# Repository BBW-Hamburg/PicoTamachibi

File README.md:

# PicoTamachibi
A Tamagotchi like toy based on PRI Pico

- The code is based on a Project from [kevinmcaleer](https://www.youtube.com/@kevinmcaleer28), the [original code can be found on his Github page](https://github.com/kevinmcaleer/picotamachibi)
- Used only for educational purposes
- *Folders:*
- contains needed libraries
- pcb_tamachibi_1-2 contains the KiCad- & gerber-files needed to create the PCBs for this project (not needed inside the Picos storage to run the project)
- raw_assets contains the graphic assets for this project (not needed inside the Picos storage to run the project)

## Setup with VSCode

It is recommended to create a new vscode profile for this type of project to have a clean editor.

VSCode will recommend extensions for this project, all of them are required to run the project.

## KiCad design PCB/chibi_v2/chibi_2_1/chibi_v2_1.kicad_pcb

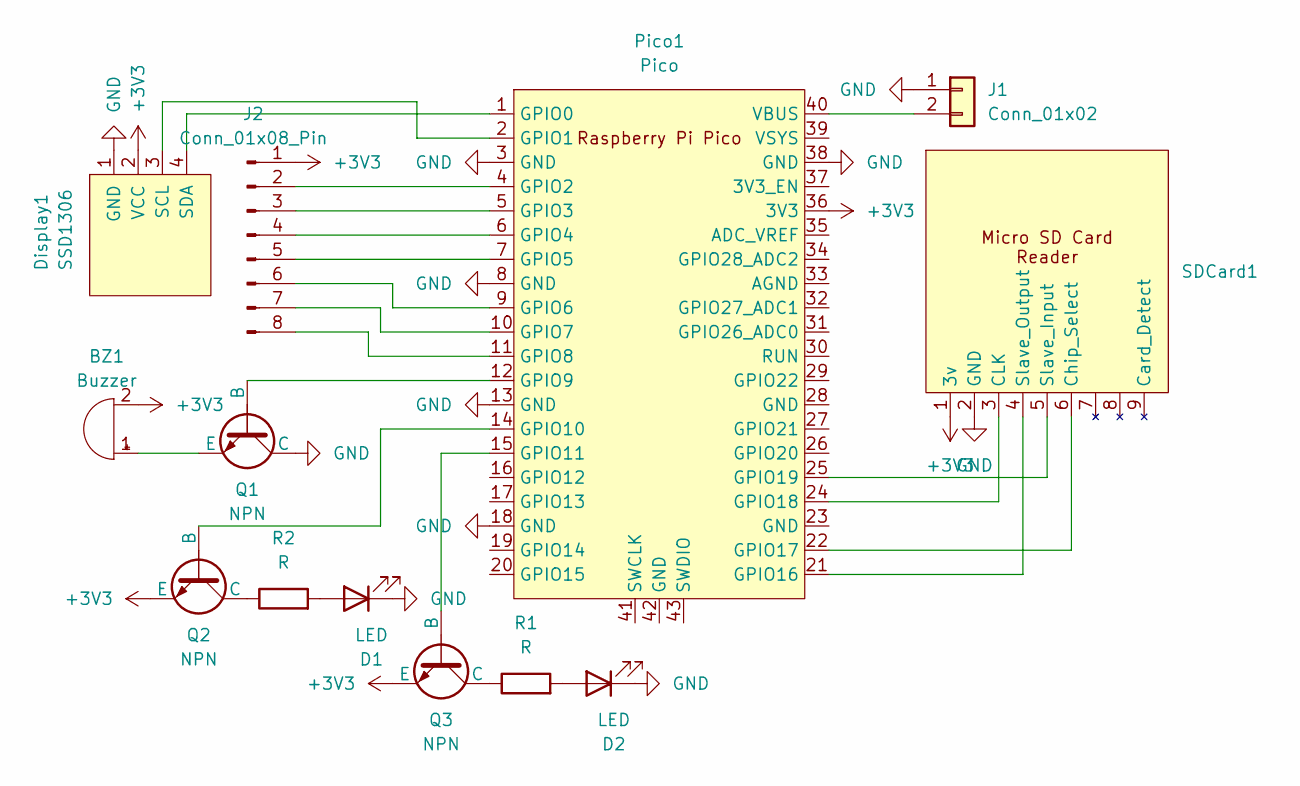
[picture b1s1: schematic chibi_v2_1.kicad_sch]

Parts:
BZ1: Buzzer; Buzzer_12x9.5RM7.6
D1, D2: LED; LED_D1.8mm_W1.8mm_H2.4mm_Horizontal_O1.27mm_Z1.6mm
Display1: SSD1306; 128x64OLED
J1: Conn_01x02; PinHeader_1x02_P2.54mm_Vertical
J2: Conn_01x08_Pin; PinHeader_1x08_P2.54mm_Vertical
Pico1: Pico; RPi_Pico_SMD_TH
Q1, Q2, Q3: NPN; TO92
R1, R2: R; R_Axial_DIN0207_L6.3mm_D2.5mm_P10.16mm_Horizontal
SDCard1: Adafruit_Micro_SD_SPI_or_SDIO_Card_Breakout_Board

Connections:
+3V3: BZ1.2 (-), Display1.2 (VCC), J2.1, Pico1.36 (3V3), Q2.3 (E), Q3.3 (E), SDCard1.1 (3v)
GND: D1.1 (K), D2.1 (K), Display1.1 (GND), J1.1, Pico1.3 (GND), Pico1.8 (GND), Pico1.13 (GND), Pico1.18 (GND), Pico1.38 (GND), Q1.1 (C), SDCard1.2 (GND)
unnamed: BZ1.1 (+), Q1.3 (E)
unnamed: D1.2 (A), R2.2
unnamed: D2.2 (A), R1.2
unnamed: Display1.3 (SCL), Pico1.2 (GPIO1)
unnamed: Display1.4 (SDA), Pico1.1 (GPIO0)
unnamed: J1.2, Pico1.40 (VBUS)
unnamed: J2.2, Pico1.4 (GPIO2)
unnamed: J2.3, Pico1.5 (GPIO3)
unnamed: J2.4, Pico1.6 (GPIO4)
unnamed: J2.5, Pico1.7 (GPIO5)
unnamed: J2.6, Pico1.9 (GPIO6)
unnamed: J2.7, Pico1.10 (GPIO7)
unnamed: J2.8, Pico1.11 (GPIO8)
unnamed: Pico1.12 (GPIO9), Q1.2 (B)
unnamed: Pico1.14 (GPIO10), Q2.2 (B)
unnamed: Pico1.15 (GPIO11), Q3.2 (B)
unnamed: Pico1.21 (GPIO16), SDCard1.4 (Slave_Output)
unnamed: Pico1.22 (GPIO17), SDCard1.6 (Chip_Select)
unnamed: Pico1.24 (GPIO18), SDCard1.3 (CLK)
unnamed: Pico1.25 (GPIO19), SDCard1.5 (Slave_Input)
unnamed: Q2.1 (C), R2.1
unnamed: Q3.1 (C), R1.1

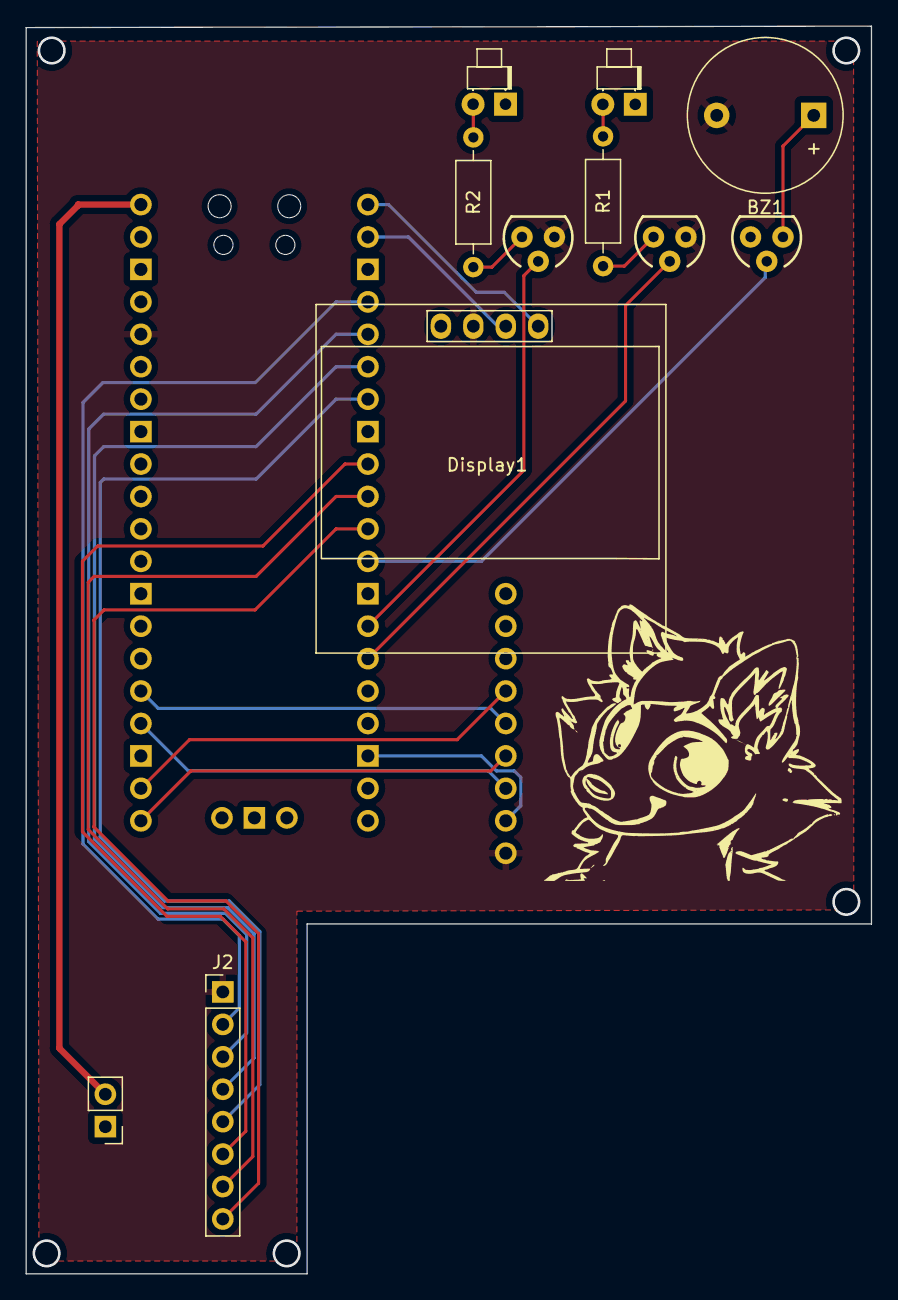
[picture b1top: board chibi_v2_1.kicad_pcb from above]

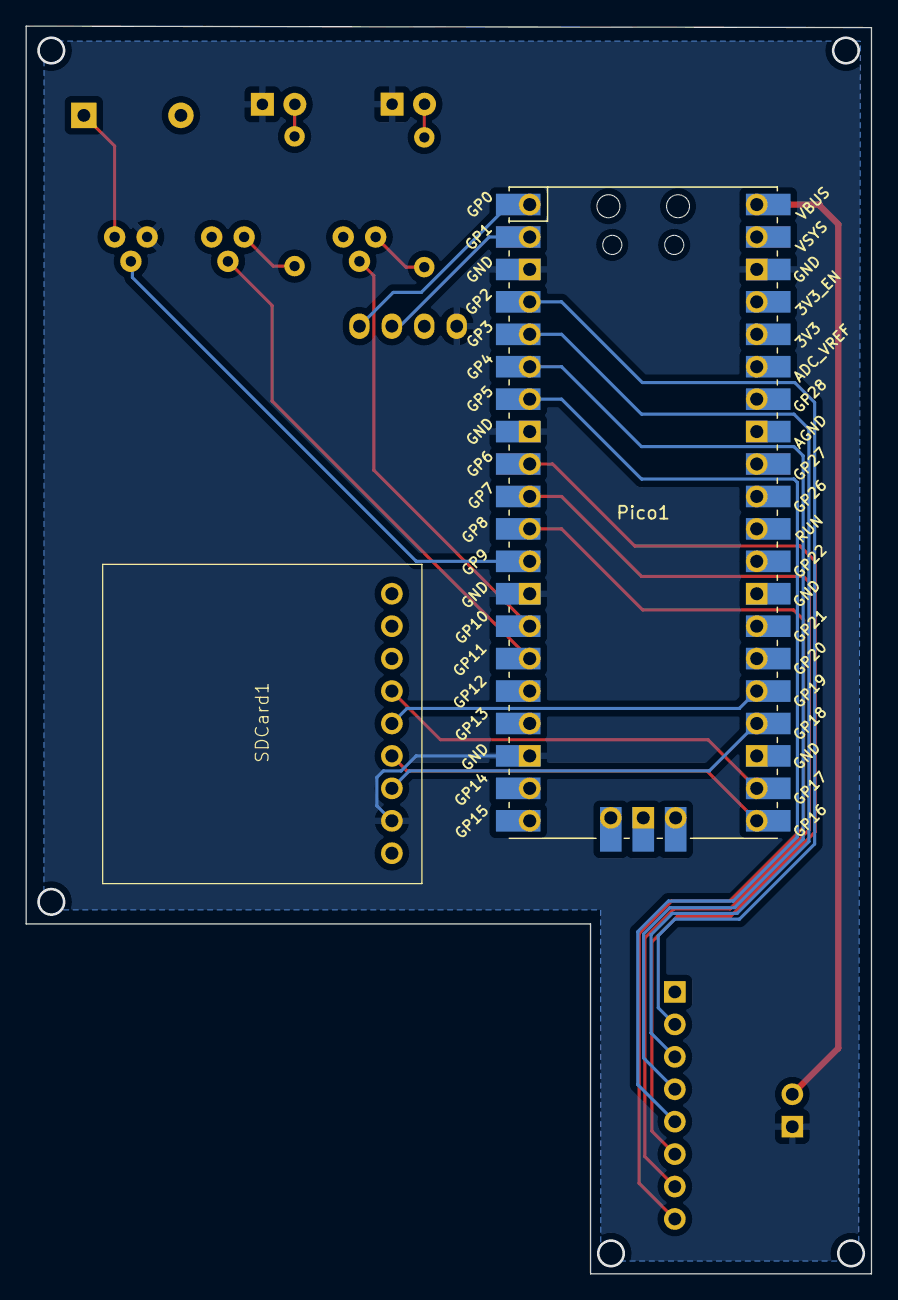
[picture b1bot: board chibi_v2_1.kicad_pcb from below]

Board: 2 copper layers, 66.2 x 97.7 mm, 13 parts (2 on the bottom side), 24 nets.

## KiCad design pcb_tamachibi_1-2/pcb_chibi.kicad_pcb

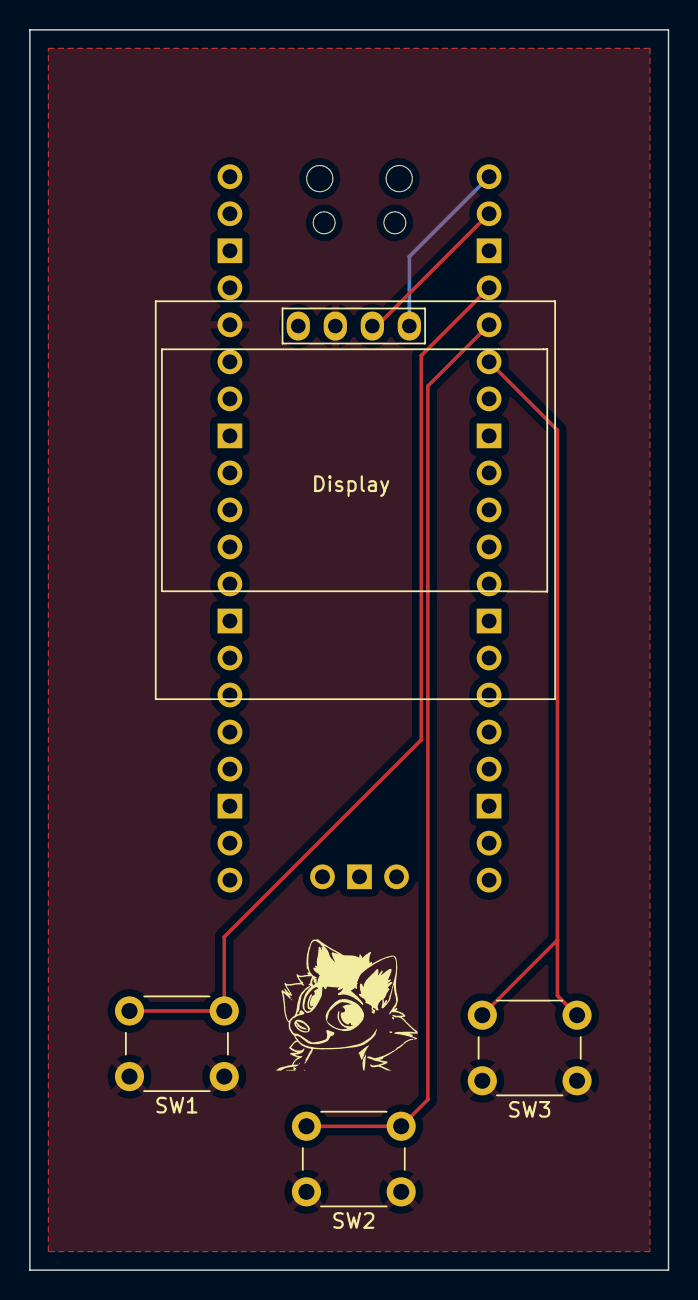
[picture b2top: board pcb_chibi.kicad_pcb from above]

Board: 2 copper layers, 43.8 x 85.1 mm, 5 parts (1 on the bottom side), 7 nets.

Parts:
Display: SSD1306; 128x64OLED
Pico: Pico; RPi_Pico_SMD_TH
SW1, SW2, SW3: SW_Push; SW_PUSH_6mm

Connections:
+3V3: Display.2 (VCC), Pico.36 (3V3), SW1.1, SW2.1, SW3.1
GND: Display.1 (GND), Pico.3 (GND), Pico.8 (GND), Pico.13 (GND), Pico.18 (GND), Pico.23 (GND), Pico.28 (GND), Pico.38 (GND)
unnamed: Display.3 (SCL), Pico.2 (GPIO1)
unnamed: Display.4 (SDA), Pico.1 (GPIO0)
unnamed: Pico.4 (GPIO2), SW1.2
unnamed: Pico.5 (GPIO3), SW2.2
unnamed: Pico.6 (GPIO4), SW3.2

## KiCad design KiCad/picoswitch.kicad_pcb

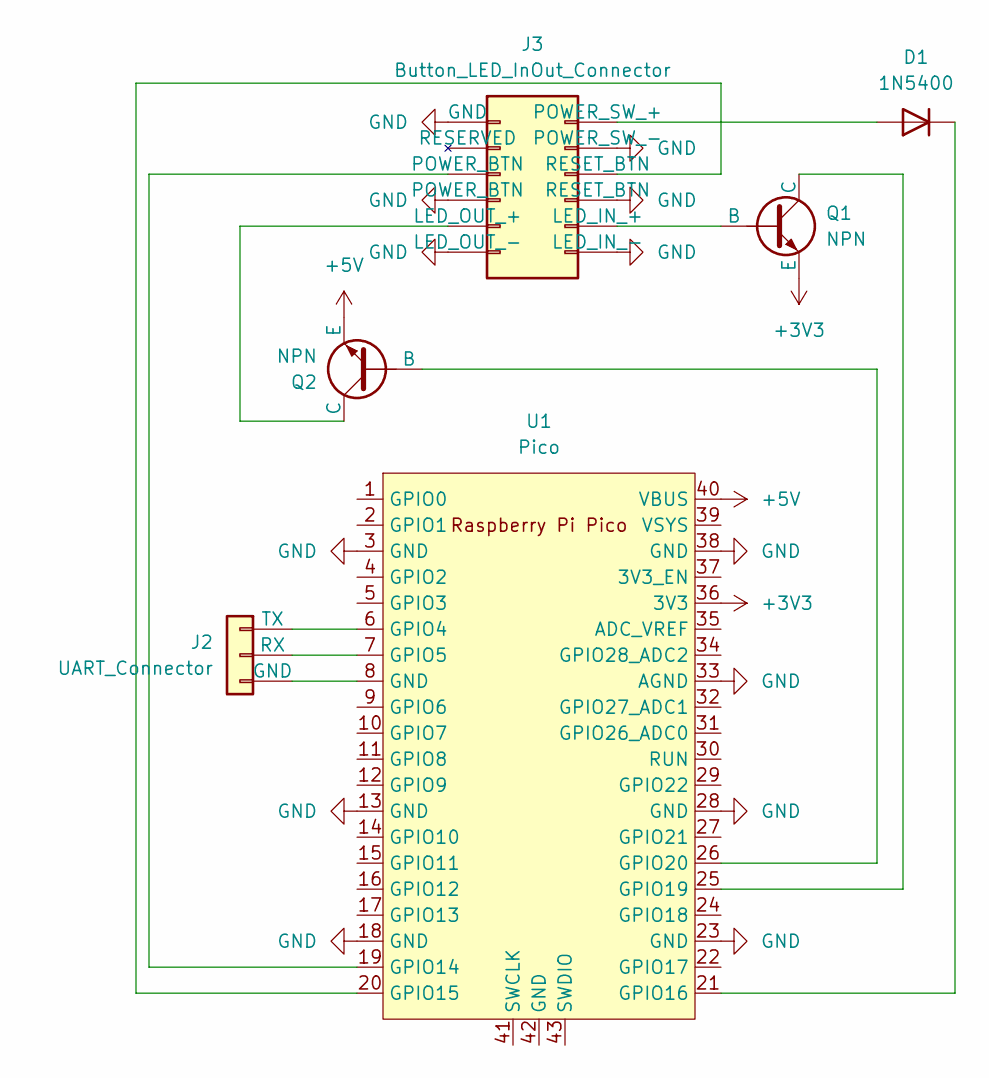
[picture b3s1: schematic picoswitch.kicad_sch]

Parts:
D1: 1N5400; D_DO-201AD_P3.81mm_Vertical_AnodeUp
J2: UART_Connector; PinSocket_1x03_P2.54mm_Vertical
J3: Button_LED_InOut_Connector; PinSocket_2x06_P2.54mm_Vertical
Q1, Q2: NPN; TO-92_Inline
U1: Pico; RPi_Pico_SMD_TH

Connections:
+3V3: Q1.3 (E), U1.36 (3V3)
+5V: Q2.3 (E), U1.40 (VBUS)
GND: J3.1 (GND), J3.4 (POWER_BTN), J3.6 (LED_OUT_-), J3.7 (LED_IN_-), J3.9 (RESET_BTN), J3.11 (POWER_SW_-), U1.3 (GND), U1.13 (GND), U1.18 (GND), U1.23 (GND), U1.28 (GND), U1.33 (AGND), U1.38 (GND)
unnamed: D1.2 (A), J3.12 (POWER_SW_+)
unnamed: D1.1 (K), U1.21 (GPIO16)
unnamed: J2.1 (GND), U1.8 (GND)
unnamed: J2.2 (RX), U1.7 (GPIO5)
unnamed: J2.3 (TX), U1.6 (GPIO4)
unnamed: J3.8 (LED_IN_+), Q1.2 (B)
unnamed: J3.5 (LED_OUT_+), Q2.1 (C)
unnamed: Q1.1 (C), U1.25 (GPIO19)
unnamed: Q2.2 (B), U1.26 (GPIO20)
unnamed: J3.3 (POWER_BTN), U1.19 (GPIO14)
unnamed: J3.10 (RESET_BTN), U1.20 (GPIO15)

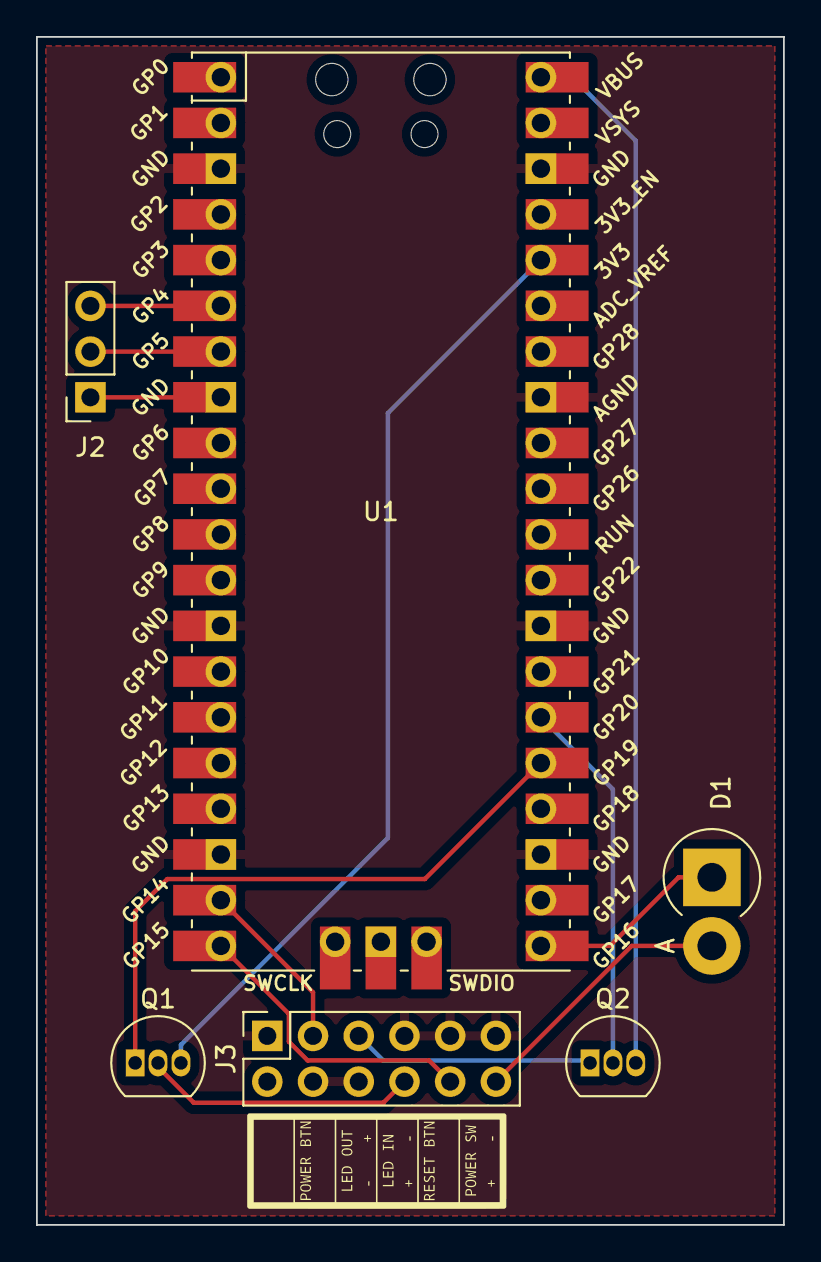
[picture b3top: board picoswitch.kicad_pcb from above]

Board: 2 copper layers, 41.5 x 66.0 mm, 6 parts (0 on the bottom side), 14 nets.

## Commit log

2024-01-19 Fixed UART
2024-01-21 Better PCB
2024-01-21 UART enhancements
2024-01-22 Remove redundant variable
2024-01-26 (Almost) full implementation
2024-01-26 Fixed pico-sdk #1
2024-01-26 Fixed pico-sdk #2
2024-01-26 Emulator and loads and loads of fixes
2024-01-26 More minor fixing
2024-01-26 Change to ETL
2024-01-27 Allocate context on stack
2024-01-27 Increased stack size now that we do everything on stack
2024-01-27 Renamed Animate::get_frame_count() to Animate::get_max_frame_index() for clarity
2024-01-27 Better main loop source mapping
2024-01-27 Increase max length of "health" strings
2024-01-27 Minor ETL tuning
2024-02-01 Fixed windows compilation (hopefully)
2024-02-01 Another attempt at fixing windows builds
2024-02-01 Another attempt
2024-02-01 Added Display::Size::buffer_size()
2024-02-01 Completely revert Windows "fix"
2024-02-01 Use ETL_NO_STL
2024-02-01 Revert last commit
2024-02-01 Enable ETL_USING_CPP20
2024-02-01 Downgrade to C++17
2024-02-01 Do not build emulator by default
2024-02-01 Fixed stack overflow in Event::popup
2024-02-01 Reuse framebuffer in popup() instead of allocating a new one
2024-02-01 Moved Event::tick() inline
2024-02-09 Initial branch commit
2024-02-11 Lots of fixes including bounce animation
2024-02-11 Fixed animation repeat check
2024-02-14 initial commit
    Added files form localy working version
2024-02-14 Update README.md
    updated text
2024-02-15 one new line for demonstarion purposes
2024-02-15 mittags aenderung am code
2024-02-15 Neuer Kommentar Z.10
2024-02-15 PCB version 1.2
2024-02-15 Initial Async Object class
2024-02-15 Completed AsyncObject implementation
2024-02-15 Removed unused async handle in Animation and allow AsyncObject handle/manager access publicly
2024-02-15 Nett hier aber waren Sie schon mal in Hamburg?
2024-02-15 _update_main.py
    Optional extended description.
2024-02-16 Update README.md
    more detailed info
2024-02-16 Started implementing logic
2024-02-16 Implemented initial toolbar controls and minor fixes
2024-02-16 Fix event callbacks not being called
2024-02-16 Add comment to main.py (#1)
2024-02-16 Fixed, now running without problems
2024-02-16 fixed? probably
2024-02-16 setup micropico config
2024-02-16 add 2 more extensions to recommendations
2024-02-16 Added AsyncObject::on_activate and restart Animation on_activate
2024-02-16 automatic soft reset on upload
2024-02-16 update settings again
2024-02-16 add pico definitions lol
2024-02-19 Implemented eating
2024-02-19 Minor adjustments to eat_food()
2024-02-22 added PCB v2 + 2_1
2024-02-23 PCB update, clearance issues solved (?)
2024-02-23 Cosmetic change, gbr + drl files generated
2024-02-23 charging pins, grb + drl files added
2024-02-23 power pins added
2024-02-23 fix nonesense type
2024-03-01 fix sdcardtest pins for new version
2024-03-01 use correct error message
2024-03-01 even better error message
2024-03-01 update sdcardtest write and load methos
2024-03-01 decrease baudrate, we wont store enough that it is required to write or read multiple megabytes
2024-03-01 show reason why there is no sdcard
2024-03-01 update stubs
2024-03-01 newest changes
2024-03-07 repositioning of a few components in PCB V2.1
